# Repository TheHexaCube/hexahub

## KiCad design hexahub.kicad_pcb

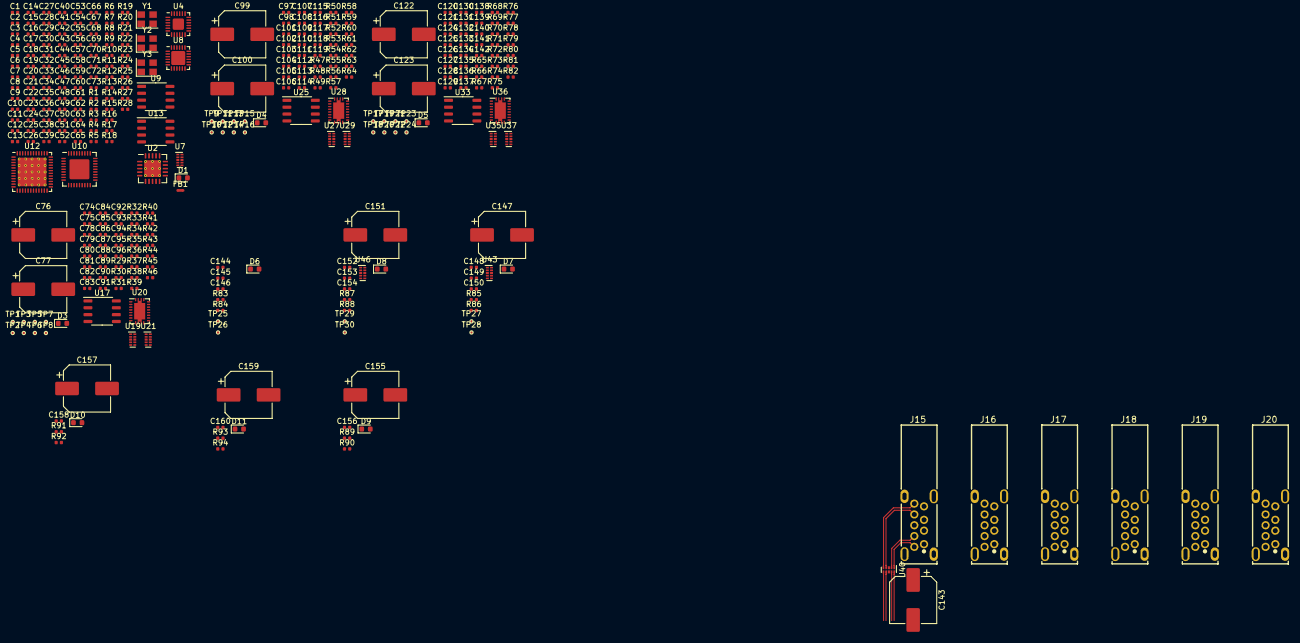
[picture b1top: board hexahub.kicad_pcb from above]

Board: 4 copper layers, 327 parts (0 on the bottom side), 168 nets.

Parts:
C1, C10: 10u; C_0402_1005Metric
C2, C3, C11, C12, C16, C18, C19, C20, C21, C22, C23, C24, C25, C26, C27, C28, C29, C30, C31, C32, C33, C34, C35, C36, C37, C38, C43, C44, C46, C47, C48, C49, C50, C51, C52, C53, C56, C57, C58, C59, C60, C62, C64, C69, C70, C73, C79, C80, C81, C88, C90, C91, C92, C93, C94, C95, C96, C102, C103, C104, C111, C113, C114, C115, C116, C117, C118, C119, C125, C126, C127, C134, C136, C137, C138, C139, C140, C141, C142, C144, C145, C146, C148, C149, C150, C152, C153, C154, C156, C158, C160: 100n; C_0402_1005Metric
C4, C13: 56p; C_0402_1005Metric
C5, C6, C14: 4u7; C_0402_1005Metric
C7: 22u; C_0402_1005Metric
C8, C17, C39, C45, C61, C63, C65, C66, C67, C68, C78, C84, C101, C107, C124, C130: 1u; C_0402_1005Metric
C9, C15: 33n; C_0402_1005Metric
C40: 2u2; C_0402_1005Metric
C41, C42, C54, C55, C71, C72: TBD; C_0402_1005Metric
C74, C75, C97, C98, C120, C121: 47n; C_0402_1005Metric
C76, C77, C99, C100, C122, C123, C143, C147, C151, C155, C157, C159: 100u; CP_Elec_8x10.5
C82, C83, C105, C106, C128, C129: 220p; C_0402_1005Metric
C85, C108, C131: 1n; C_0402_1005Metric
C86, C87, C109, C110, C132, C133: DNP; C_0402_1005Metric
C89, C112, C135: 100p; C_0402_1005Metric
D1, D6, D7, D8, D9, D10, D11: VBUS05B1-SD0; D_0603_1608Metric
D3, D4, D5: TBD; D_0603_1608Metric
FB1: DNP; NetTie-2_SMD_Pad0.5mm
J15, J16, J17, J18, J19, J20: USB3_A; USB3_A-TH_U231-091N-4BLCC14-S-5
R1, R2, R9, R10, R41, R42, R59, R60, R77, R78: DNP; R_0402_1005Metric
R3: 8k66; R_0402_1005Metric
R4: 5k; R_0402_1005Metric
R5, R6, R8, R12, R14, R15, R18, R21, R22, R23, R31, R32, R33, R36, R37, R38, R49, R50, R51, R54, R55, R56, R67, R68, R69, R72, R73, R74: 10k; R_0402_1005Metric
R7, R13: 20k; R_0402_1005Metric
R11: 30k9; R_0402_1005Metric
R16, R17, R24, R45, R63, R81: 100k; R_0402_1005Metric
R19, R46, R64, R82, R84, R86, R88, R90, R92, R94: 300R; R_0402_1005Metric
R20: 1k; R_0402_1005Metric
R25, R26: 12k; R_0402_1005Metric
R27: 150k; R_0402_1005Metric
R28: 680R; R_0402_1005Metric
R29, R47, R65: 5m; R_0402_1005Metric
R30, R48, R66: 10m; R_0402_1005Metric
R34, R35, R39, R40, R52, R53, R57, R58, R70, R71, R75, R76: 30R1; R_0402_1005Metric
R43, R44, R61, R62, R79, R80: 50k; R_0402_1005Metric
R83, R85, R87, R89, R91, R93: 33k2; R_0402_1005Metric
TP1, TP2, TP3, TP4, TP5, TP6, TP7, TP8, TP9, TP10, TP11, TP12, TP13, TP14, TP15, TP16, TP17, TP18, TP19, TP20, TP21, TP22, TP23, TP24, TP25, TP26, TP27, TP28, TP29, TP30: TestPoint_Small; TestPoint_Pad_D0.5mm
U2: TPS74801DRCT; TQFN-20-1EP_5x5mm_P0.65mm_EP3.1x3.1mm_ThermalVias
U4: TCA9548AMRGER; Texas_RGE0024C_EP2.1x2.1mm
U7, U19, U21, U27, U29, U35, U37, U40, U43, U46: TPD4E02B04; USON-10_2.5x1.0mm_P0.5mm
U8: ATtiny3227-M; QFN-24-1EP_4x4mm_P0.5mm_EP2.6x2.6mm
U9, U13, U17, U25, U33: GD25D10CT; SOP-8_3.9x4.9mm_P1.27mm
U10: USB2514B_Bi; QFN-36-1EP_6x6mm_P0.5mm_EP3.7x3.7mm
U12: GL3224; QFN-48-1EP_7x7mm_P0.5mm_EP5.3x5.3mm_ThermalVias
U20, U28, U36: HD3SS3212; Texas_VQFN-RHL-20
Y1, Y3: 25MHz; Crystal_SMD_Abracon_ABM8G-4Pin_3.2x2.5mm
Y2: 24MHz; Crystal_SMD_Abracon_ABM8G-4Pin_3.2x2.5mm

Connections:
+1V2: C8.1, C26.1, C27.1, C28.1, C29.1, C30.1, C31.1, C32.1, C33.1, C34.1, C35.1, C36.1, C37.1, C38.1, C39.1, R4.1, U2.1 (OUT), U2.18 (OUT), U2.19 (OUT), U2.20 (OUT)
+1V5: C5.1, C6.1, C7.1, U2.5 (IN), U2.6 (IN), U2.7 (IN), U2.8 (IN), U2.11 (EN)
+3V3: C14.1, C16.1, C17.1, C18.1, C19.1, C20.1, C21.1, C22.1, C23.1, C24.1, C25.1, C43.1, C50.1, C51.1, C52.1, C53.1, C73.1, C78.1, C79.1, C90.1, C94.1, C101.1, C102.1, C113.1, C117.1, C124.1, C125.1, C136.1, C140.1, FB1.2, R5.1, R14.2, R15.2, R21.2, R22.2, R23.2, R32.1, R33.1, R50.1, R51.1, R68.1, R69.1, U4.21 (VCC), U8.4 (VCC), U9.3 (~WP), U9.8 (VCC), U13.3 (~WP), U13.8 (VCC), U17.3 (~WP), U17.8 (VCC), U20.6 (VCC), U25.3 (~WP), U25.8 (VCC), U28.6 (VCC), U33.3 (~WP), U33.8 (VCC), U36.6 (VCC)
+24V: C1.1, C2.1, C10.1, C11.1, R1.1, R9.1, R29.1, R39.2, R47.1, R57.2, R65.1, R75.2
/USB2_Port_7/D+: J18.2 (D-), U10.2 (USBDP_DN1/PRT_DIS_P1)
/USB2_Port_7/D-: J18.3 (D+), U10.1 (USBDM_DN1/PRT_DIS_M1)
/USB2_Port_8/D+: J19.2 (D-), U10.4 (USBDP_DN2/PRT_DIS_P2)
/USB2_Port_8/D-: J19.3 (D+), U10.3 (USBDM_DN2/PRT_DIS_M2)
/USB2_Port_9/D+: J20.2 (D-), U10.7 (USBDP_DN3/PRT_DIS_P3)
/USB2_Port_9/D-: J20.3 (D+), U10.6 (USBDM_DN3/PRT_DIS_M3)
/USB3_Port_4/SS_RX+: C145.1, C145.2, J15.8 (SSTX-), U40.2 (I2), U40.9 (O2)
/USB3_Port_4/SS_RX-: C144.1, C144.2, J15.9 (SSTX+), U40.1 (I1), U40.10 (O1)
/USB3_Port_4/SS_TX+: J15.5 (SSRX-), U40.5 (I4), U40.6 (O4)
/USB3_Port_4/SS_TX-: J15.6 (SSRX+), U40.4 (I3), U40.7 (O3)
/USB3_Port_6/SS_RX+: C149.1, C149.2, J16.8 (SSTX-), U43.2 (I2), U43.9 (O2)
/USB3_Port_6/SS_RX-: C148.1, C148.2, J16.9 (SSTX+), U43.1 (I1), U43.10 (O1)
/USB3_Port_6/SS_TX+: J16.5 (SSRX-), U43.5 (I4), U43.6 (O4)
/USB3_Port_6/SS_TX-: J16.6 (SSRX+), U43.4 (I3), U43.7 (O3)
/USB3_Port_7/SS_RX+: C153.1, C153.2, J17.8 (SSTX-), U46.2 (I2), U46.9 (O2)
/USB3_Port_7/SS_RX-: C152.1, C152.2, J17.9 (SSTX+), U46.1 (I1), U46.10 (O1)
/USB3_Port_7/SS_TX+: J17.5 (SSRX-), U46.5 (I4), U46.6 (O4)
/USB3_Port_7/SS_TX-: J17.6 (SSRX+), U46.4 (I3), U46.7 (O3)
GND: C1.2, C2.2, C6.2, C7.2, C8.2, C9.2, C10.2, C11.2, C14.2, C15.2, C16.2, C17.2, C18.2, C19.2, C20.2, C21.2, C22.2, C23.2, C24.2, C25.2, C26.2, C27.2, C28.2, C29.2, C30.2, C31.2, C32.2, C33.2, C34.2, C35.2, C36.2, C37.2, C38.2, C39.2, C40.2, C41.2, C42.2, C43.2, C44.1, C50.2, C51.2, C52.2, C53.2, C54.2, C55.2, C56.2, C57.2, C58.2, C59.2, C60.2, C61.2, C62.2, C63.2, C64.2, C65.2, C66.2, C67.2, C68.2, C71.2, C72.2, C73.2, C76.2, C77.2, C78.2, C79.2, C82.2, C83.2, C84.2, C86.2, C87.2, C88.2, C89.2, C90.2, C94.2, C96.1, C99.2, C100.2, C101.2, C102.2, C105.2, C106.2, C107.2, C109.2, C110.2, C111.2, C112.2, C113.2, C117.2, C119.1, C122.2, C123.2, C124.2, C125.2, C128.2, C129.2, C130.2, C132.2, C133.2, C134.2, C135.2, C136.2, C140.2, C142.1, C143.2, C146.1, C147.2, C150.1, C151.2, C154.1, C155.2, C156.1, C157.2, C158.1, C159.2, C160.1, D1.1 (A1), D3.1 (A1), D4.1 (A1), D5.1 (A1), D6.1 (A1), D7.1 (A1), D8.1 (A1), D9.1 (A1), D10.1 (A1), D11.1 (A1), J15.4 (GND), J15.7 (DRAIN), J16.4 (GND), J16.7 (DRAIN), J17.4 (GND), J17.7 (DRAIN), J18.4 (GND), J18.7 (DRAIN), J19.4 (GND), J19.7 (DRAIN), J20.4 (GND), J20.7 (DRAIN), R2.2, R6.2, R7.2, R8.2, R10.2, R12.2, R13.2, R17.1, R19.1, R24.1, R25.1, R26.1, R27.1, R28.1, R36.2, R37.2, R38.2, R43.2, R44.2, R45.2, R46.1, R54.2, R55.2, R56.2, R61.2, R62.2, R63.2, R64.1, R72.2, R73.2, R74.2, R79.2, R80.2, R81.2, R82.1, R83.2, R84.1, R85.2, R86.1, R87.2, R88.1, R89.2, R90.1, R91.2, R92.1, R93.2, R94.1, U2.2 (NC), U2.3 (NC), U2.4 (NC), U2.12 (GND), U2.13 (NC), U2.14 (NC), U2.17 (NC), U4.9 (GND), U4.18 (A2), U4.22 (A0), U4.23 (A1), U7.3 (GND), U7.8 (GND), U8.3 (GND), U8.25 (GND), U9.4 (GND), U10.37 (VSS), U12.3 (GND), U12.12 (GND), U12.49 (GND), U13.4 (GND), U17.4 (GND), U19.3 (GND), U19.8 (GND), U20.2 (OEn), U20.5 (GND), U20.11 (GND), U20.20 (GND), U21.3 (GND), U21.8 (GND), U25.4 (GND), U27.3 (GND), U27.8 (GND), U28.2 (OEn), U28.5 (GND), U28.11 (GND), U28.20 (GND), U29.3 (GND), U29.8 (GND), U33.4 (GND), U35.3 (GND), U35.8 (GND), U36.2 (OEn), U36.5 (GND), U36.11 (GND), U36.20 (GND), U37.3 (GND), U37.8 (GND), U40.3 (GND), U40.8 (GND), U43.3 (GND), U43.8 (GND), U46.3 (GND), U46.8 (GND), Y1.2, Y1.4, Y2.2, Y2.4, Y3.2, Y3.4
HUB1_VBUS_DET: R16.2, R17.2, U10.27 (VBUS_DET)
HUB1_~RST: R23.1, U10.26 (RESET_N)
I2C_CLK: R22.1, U4.20 (SDA), U8.16 (PB0), U10.24 (SCL/SMBCLK/CFG_SEL0)
I2C_DATA: R21.1, U4.19 (SCL), U8.15 (PB1), U10.22 (SDA/SMBDATA/NON_REM1)
unnamed: C4.1, R3.1
unnamed: C13.1, R11.1
unnamed: C45.1, C46.1, C47.1, C48.1, C49.1, FB1.1, U10.5 (VDDA33), U10.10 (VDDA33), U10.15 (VDD33), U10.23 (VDD33), U10.29 (VDDA33), U10.36 (VDDA33)
unnamed: C45.2, C46.2, C47.2, C48.2, C49.2
unnamed: C58.1, C59.1, C60.1, C61.1, U12.25 (VDD33), U12.34 (VDD33), U12.44 (VDD33)
unnamed: C65.1, C66.1, U12.6 (AVDD33), U12.15 (AVDD33)
unnamed: C85.2, R45.1
unnamed: C86.1, R41.2
unnamed: C87.1, R42.2
unnamed: C108.2, R63.1
unnamed: C109.1, R59.2
unnamed: C110.1, R60.2
unnamed: C131.2, R81.1
unnamed: C132.1, R77.2
unnamed: C133.1, R78.2
unnamed: C40.1, D1.2 (A2), R16.1
unnamed: C76.1, D3.2 (A2), TP4.1
unnamed: C99.1, D4.2 (A2), TP12.1
unnamed: C122.1, D5.2 (A2), TP20.1
unnamed: C143.1, D6.2 (A2), J15.1 (VBUS), TP25.1
unnamed: C147.1, D7.2 (A2), J16.1 (VBUS), TP27.1
unnamed: C151.1, D8.2 (A2), J17.1 (VBUS), TP29.1
unnamed: C155.1, D9.2 (A2), J18.1 (VBUS)
unnamed: C157.1, D10.2 (A2), J19.1 (VBUS)
unnamed: C159.1, D11.2 (A2), J20.1 (VBUS)
unnamed: C44.2, R19.2
unnamed: C96.2, R46.2
unnamed: C119.2, R64.2
unnamed: C142.2, R82.2
unnamed: C146.2, J15.10 (SHIELD), R84.2
unnamed: C150.2, J16.10 (SHIELD), R86.2
unnamed: C154.2, J17.10 (SHIELD), R88.2
unnamed: C156.2, J18.10 (SHIELD), R90.2
unnamed: C158.2, J19.10 (SHIELD), R92.2
unnamed: C160.2, J20.10 (SHIELD), R94.2
unnamed: R30.2, R31.1, R40.2, TP2.1
unnamed: R48.2, R49.1, R58.2, TP10.1
unnamed: R66.2, R67.1, R76.2, TP18.1
unnamed: R30.1, R35.2
unnamed: R48.1, R53.2
unnamed: R66.1, R71.2
unnamed: R1.2, R2.1
unnamed: C4.2, R3.2, R6.1
unnamed: C5.2, U2.10 (BIAS)
unnamed: R4.2, R8.1, U2.16 (FB)
unnamed: R5.2, U2.9 (PG)
unnamed: R9.2, R10.1
unnamed: C13.2, R11.2, R12.1
unnamed: R14.1, U4.24 (~RESET)
unnamed: R24.2, U9.6 (SCLK)
unnamed: C41.1, Y1.3
unnamed: C42.1, Y1.1
unnamed: R18.1, R20.2, U8.23 (~RESET/PA0)
unnamed: C57.1, U10.14 (CRFILT)
unnamed: C56.1, U10.34 (PLLFILT)
unnamed: R26.2, U10.35 (RBIAS)
unnamed: C54.1, U10.33 (XTALIN/CLKIN), Y2.3
unnamed: C55.1, U10.32 (XTALOUT), Y2.1
unnamed: C63.1, C64.1, U12.9 (AVDD12)
unnamed: R28.2, U12.16 (RTERM)
unnamed: C70.2, U12.11 (RX+)
unnamed: C69.2, U12.10 (RX-)
unnamed: U12.19 (SPI_CK), U13.6 (SCLK)
unnamed: U12.20 (SPI_CS), U13.1 (~CS)
unnamed: U12.17 (SPI_MISO), U13.2 (O1/SO)
unnamed: U12.18 (SPI_MOSI), U13.5 (SI/IO0)
unnamed: C62.1, U12.26 (VDD12)
unnamed: C67.1, U12.43 (VUHS_1)
unnamed: C68.1, U12.33 (VUHS_2)
unnamed: C71.1, U12.13 (XI), Y3.3
unnamed: C72.1, U12.14 (XO), Y3.1
unnamed: R32.2, R36.1
unnamed: R33.2, R37.1
unnamed: C85.1, C89.1
unnamed: R41.1, R43.1
unnamed: C80.1, R34.1
unnamed: C80.2, R39.1
unnamed: R42.1, R44.1
unnamed: C81.2, R40.1
unnamed: C81.1, R35.1
unnamed: R29.2, R34.2, TP1.1
unnamed: U19.1 (I1), U20.19 (B0+)
unnamed: U19.2 (I2), U20.18 (B0-)
unnamed: U19.4 (I3), U20.17 (B1+)
unnamed: U19.5 (I4), U20.16 (B1-)
unnamed: C91.1, U19.7 (O3)
unnamed: C92.1, U19.6 (O4)
unnamed: U20.15 (C0+), U21.1 (I1)
unnamed: U20.14 (C0-), U21.2 (I2)
unnamed: U20.13 (C1+), U21.4 (I3)
unnamed: U20.12 (C1-), U21.5 (I4)
unnamed: C95.1, U21.7 (O3)
unnamed: C93.1, U21.6 (O4)
unnamed: R50.2, R54.1
unnamed: R51.2, R55.1
unnamed: C108.1, C112.1
unnamed: R59.1, R61.1
unnamed: C103.1, R52.1
unnamed: C103.2, R57.1
unnamed: R60.1, R62.1
unnamed: C104.2, R58.1
unnamed: C104.1, R53.1
unnamed: R47.2, R52.2, TP9.1
unnamed: U27.1 (I1), U28.19 (B0+)
unnamed: U27.2 (I2), U28.18 (B0-)
unnamed: U27.4 (I3), U28.17 (B1+)
unnamed: U27.5 (I4), U28.16 (B1-)
unnamed: C114.1, U27.7 (O3)
unnamed: C115.1, U27.6 (O4)
unnamed: U28.15 (C0+), U29.1 (I1)
unnamed: U28.14 (C0-), U29.2 (I2)
unnamed: U28.13 (C1+), U29.4 (I3)
unnamed: U28.12 (C1-), U29.5 (I4)
unnamed: C118.1, U29.7 (O3)
unnamed: C116.1, U29.6 (O4)
unnamed: R68.2, R72.1
unnamed: R69.2, R73.1
unnamed: C131.1, C135.1
unnamed: R77.1, R79.1
unnamed: C126.1, R70.1
unnamed: C126.2, R75.1
unnamed: R78.1, R80.1
unnamed: C127.2, R76.1
unnamed: C127.1, R71.1
unnamed: R65.2, R70.2, TP17.1
unnamed: U35.1 (I1), U36.19 (B0+)
unnamed: U35.2 (I2), U36.18 (B0-)
unnamed: U35.4 (I3), U36.17 (B1+)
unnamed: U35.5 (I4), U36.16 (B1-)
unnamed: C137.1, U35.7 (O3)
unnamed: C138.1, U35.6 (O4)
unnamed: U36.15 (C0+), U37.1 (I1)
unnamed: U36.14 (C0-), U37.2 (I2)
unnamed: U36.13 (C1+), U37.4 (I3)
unnamed: U36.12 (C1-), U37.5 (I4)
unnamed: C141.1, U37.7 (O3)
unnamed: C139.1, U37.6 (O4)
PP_HV2: C77.1, C100.1, C123.1, TP3.1, TP11.1, TP19.1
VBUS_EN_P1: R38.1, TP5.1
VBUS_EN_P2: R56.1, TP13.1
VBUS_EN_P3: R74.1, TP21.1

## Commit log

2023-11-18 more parts
2023-11-19 work
2023-11-24 stuff
2023-12-03 GL3224
2023-12-07 layout
